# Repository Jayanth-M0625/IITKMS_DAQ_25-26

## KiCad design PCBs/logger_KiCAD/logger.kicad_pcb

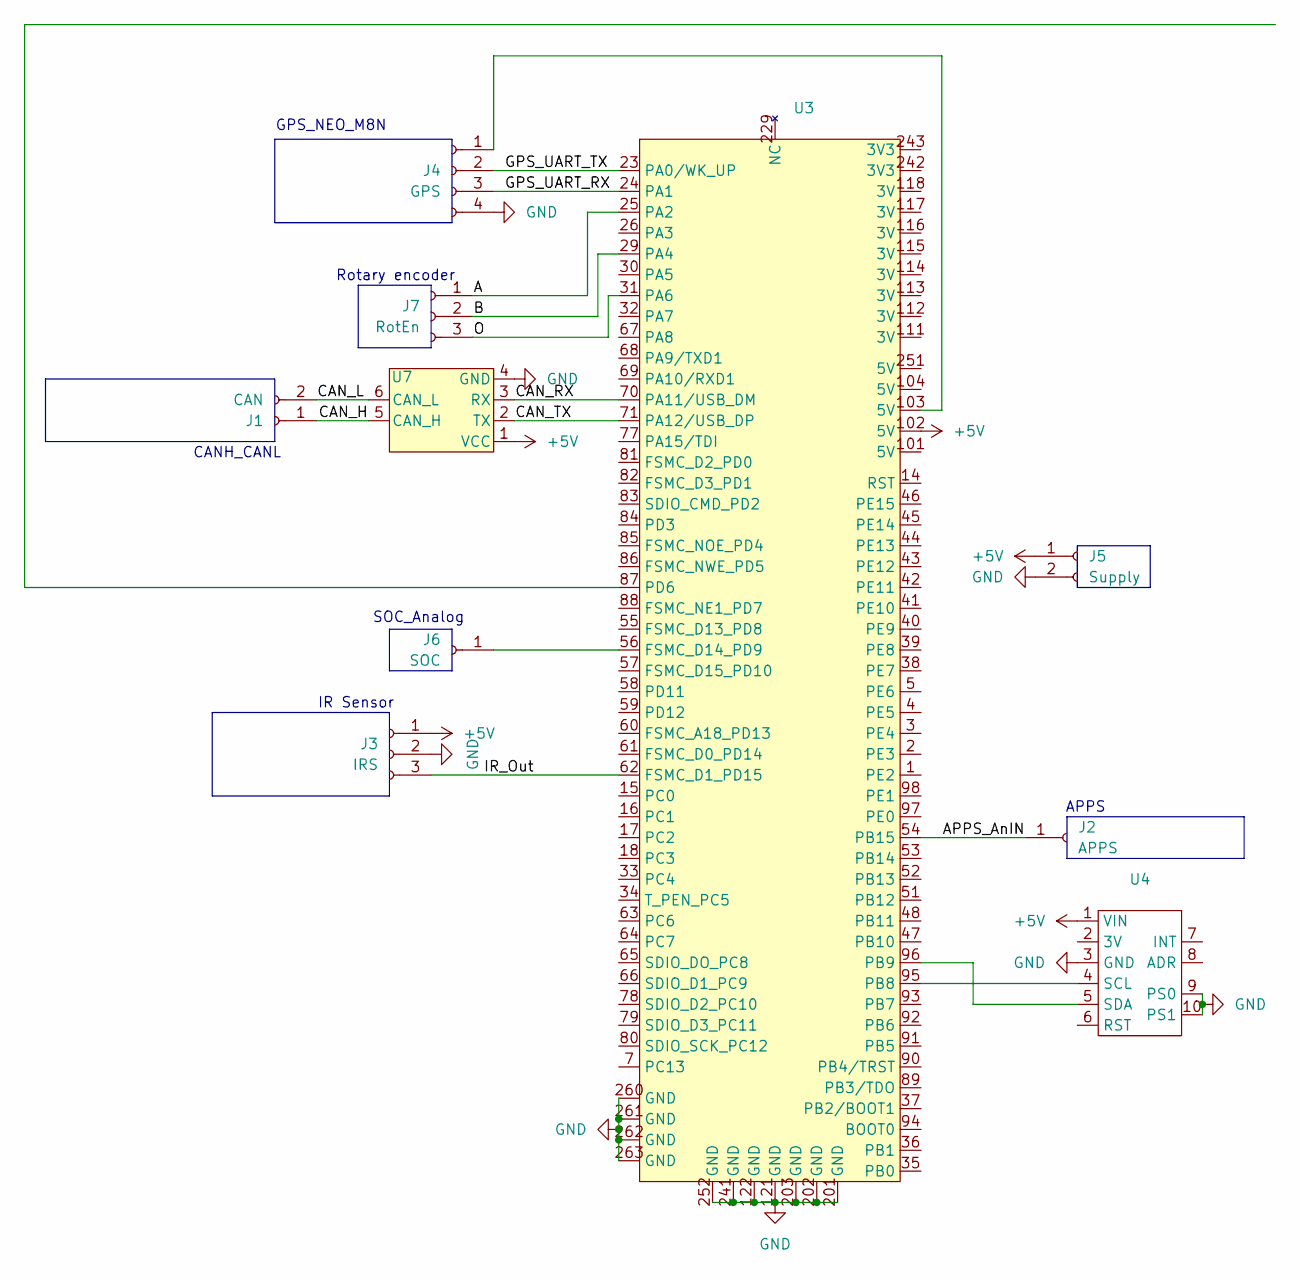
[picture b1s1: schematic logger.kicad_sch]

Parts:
J1: CAN; PinHeader_1x02_P2.54mm_Vertical
J2: APPS; PinHeader_1x01_P2.54mm_Vertical
J3: IRS; PinHeader_1x03_P2.54mm_Vertical
J4: GPS; PinSocket_1x04_P2.54mm_Vertical
J5: Supply; PinHeader_1x02_P2.54mm_Vertical
J6: SOC; PinHeader_1x01_P2.54mm_Vertical
J7: RotEn; PinHeader_1x03_P2.54mm_Vertical
U3: STM32F4VE_blackBoard
U4: BNO055_IMU
U7: TJA1050

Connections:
+5V: J3.1, J5.1, U3.102 (5V), U4.1 (VIN), U7.1 (VCC)
/A: J7.1, U3.25 (PA2)
/APPS_AnIN: J2.1, U3.54 (PB15)
/B: J7.2, U3.29 (PA4)
/CAN_H: J1.1, U7.5 (CAN_H)
/CAN_L: J1.2, U7.6 (CAN_L)
/CAN_RX: U3.70 (PA11/USB_DM), U7.3 (RX)
/CAN_TX: U3.71 (PA12/USB_DP), U7.2 (TX)
/GPS_UART_RX: J4.3, U3.24 (PA1)
/GPS_UART_TX: J4.2, U3.23 (PA0/WK_UP)
/IR_Out: J3.3, U3.62 (FSMC_D1_PD15)
/O: J7.3, U3.31 (PA6)
GND: J3.2, J4.4, J5.2, U3.121 (GND), U3.122 (GND), U3.201 (GND), U3.202 (GND), U3.203 (GND), U3.241 (GND), U3.252 (GND), U3.260 (GND), U3.261 (GND), U3.262 (GND), U3.263 (GND), U4.3 (GND), U4.9 (PS0), U4.10 (PS1), U7.4 (GND)
unnamed: J4.1, U3.103 (5V)
unnamed: J6.1, U3.56 (FSMC_D14_PD9)
unnamed: U3.95 (PB8), U4.4 (SCL)
unnamed: U3.96 (PB9), U4.5 (SDA)

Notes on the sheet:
IR Sensor
Rotary encoder
CANH_CANL
GPS_NEO_M8N
APPS
SOC_Analog

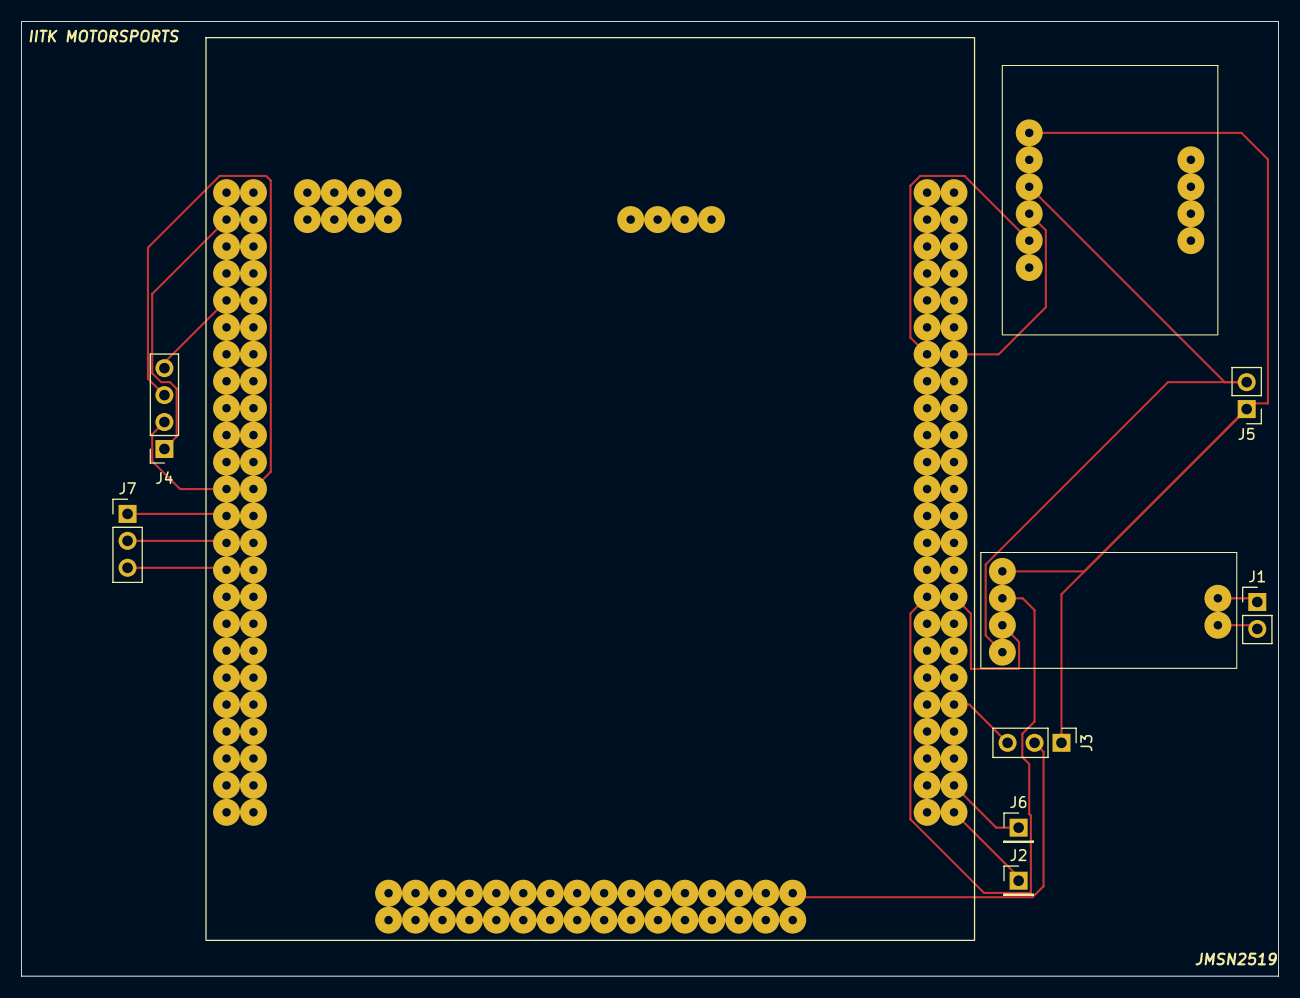
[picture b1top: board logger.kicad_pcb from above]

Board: 2 copper layers, 118.5 x 90.0 mm, 10 parts (0 on the bottom side), 17 nets.
